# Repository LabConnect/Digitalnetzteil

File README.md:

Digitalnetzteil
============

In diesem Repository werden die Daten zum Digitalnetzteil zu finden sein.

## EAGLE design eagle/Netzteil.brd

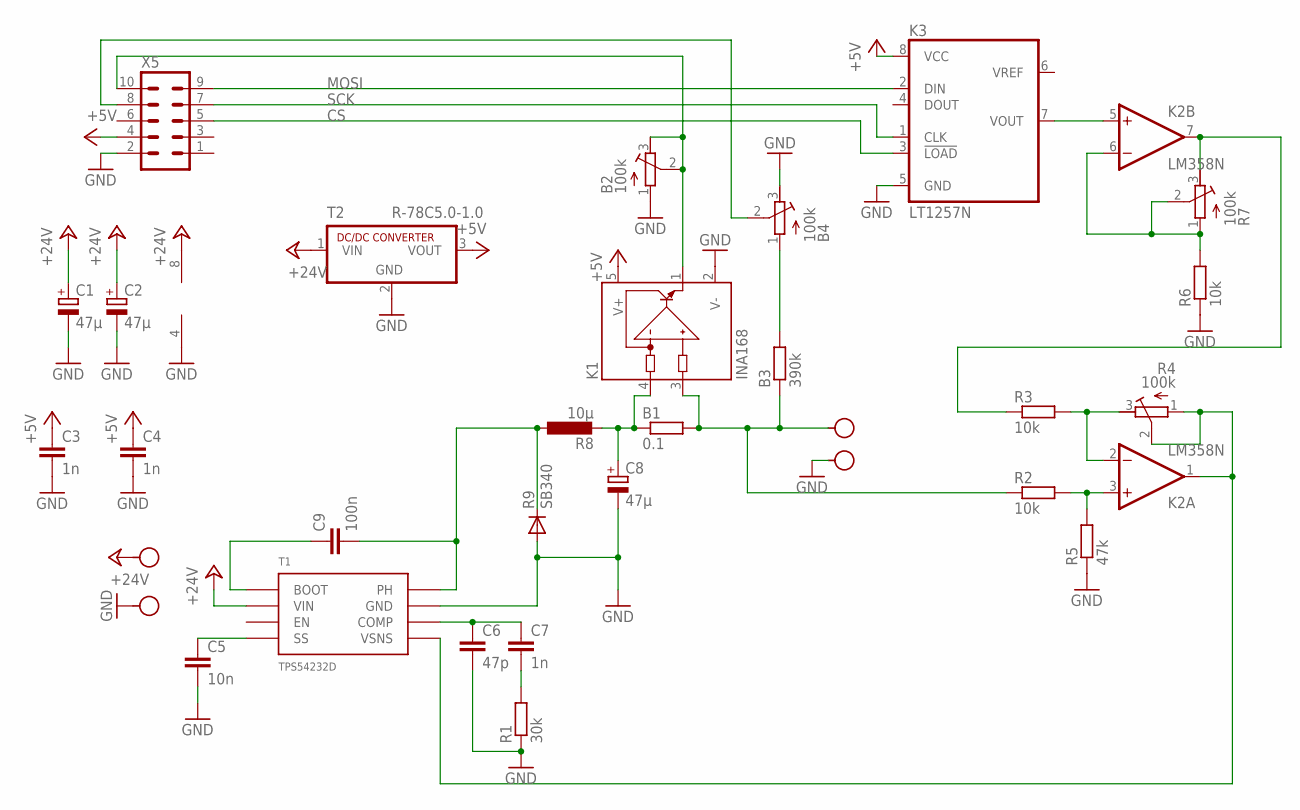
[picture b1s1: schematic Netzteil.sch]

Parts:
B1: 0.1; P0817/22
B2, B4: 100k; RTRIM64Y
B3: 390k; 0309/12
C1, C2, C8: 47µ; E2,5-6
C3, C4, C7: 1n; C025-025X050
C5: 10n; C025-025X050
C6: 47p; C025-025X050
C9: 100n; C025-025X050
K1: INA168; SOT23-5
K2: LM358N; DIL08
K3: LT1257N; DIL08
R1: 30k; 0309/12
R2, R3, R6: 10k; 0309/12
R4, R7: 100k; RTRIM64Y
R5: 47k; 0309/12
R8: 10µ; PIS2816
R9: SB340; DO201-15
T1: TPS54232D; SOIC-8
T2: R-78C5.0-1.0; SIP3; MPN R-78C5.0-1.0
X1, X2, X3, X4: SEW_HOLE-SMALL; SIMPLE_HOLE_SM
X5: ML10

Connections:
+5V: C3.1, C4.1, K1.5 (V+), K3.8 (VCC), T2.3 (VOUT), X5.4
+24V: C1.+, C2.+, K2.8 (V+), T1.2 (VIN), T2.1 (VIN), X1.P$1
CS: K3.3 (!LOAD), X5.5
GND: B2.1 (E), B4.3 (A), C1.-, C2.-, C3.2, C4.2, C5.2, C6.2, C8.-, K1.2 (V-), K2.4 (V-), K3.5 (GND), R1.1, R5.1, R6.1, R9.A, T1.7 (GND), T2.2 (GND), X2.P$1, X4.P$1, X5.2
MOSI: K3.2 (DIN), X5.9
unnamed: B1.1, C8.+, K1.4 (IN-), R8.2
unnamed: C9.2, R8.1, R9.C, T1.8 (PH)
unnamed: C5.1, T1.4 (SS)
unnamed: K2.7 (OUT), R3.1, R7.3 (A)
unnamed: C7.2, R1.2
unnamed: B1.2, B3.1, K1.3 (IN+), R2.1, X3.P$1
unnamed: C6.1, C7.1, T1.6 (COMP)
unnamed: B3.2, B4.1 (E)
unnamed: B4.2 (S), X5.8
unnamed: K2.1 (OUT), R4.1 (E), R4.2 (S), T1.5 (VSNS)
unnamed: K2.5 (+IN), K3.7 (VOUT)
unnamed: K2.6 (-IN), R6.2, R7.1 (E), R7.2 (S)
unnamed: K2.2 (-IN), R3.2, R4.3 (A)
unnamed: K2.3 (+IN), R2.2, R5.2
unnamed: B2.2 (S), B2.3 (A), K1.1 (OUT), X5.10
unnamed: C9.1, T1.1 (BOOT)
SCK: K3.1 (CLK), X5.7

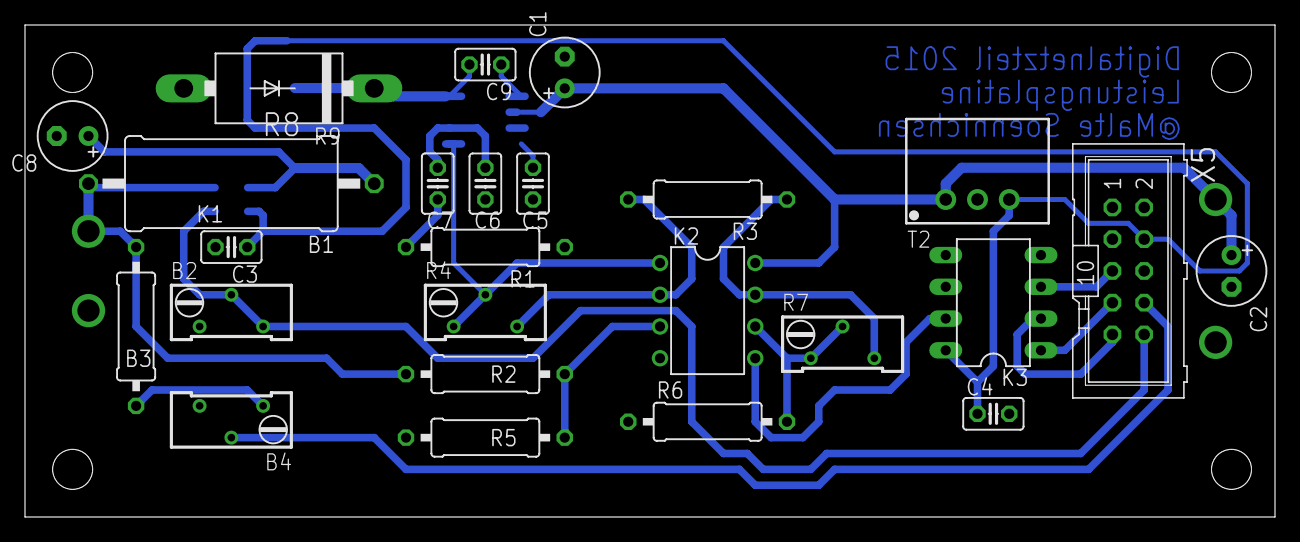
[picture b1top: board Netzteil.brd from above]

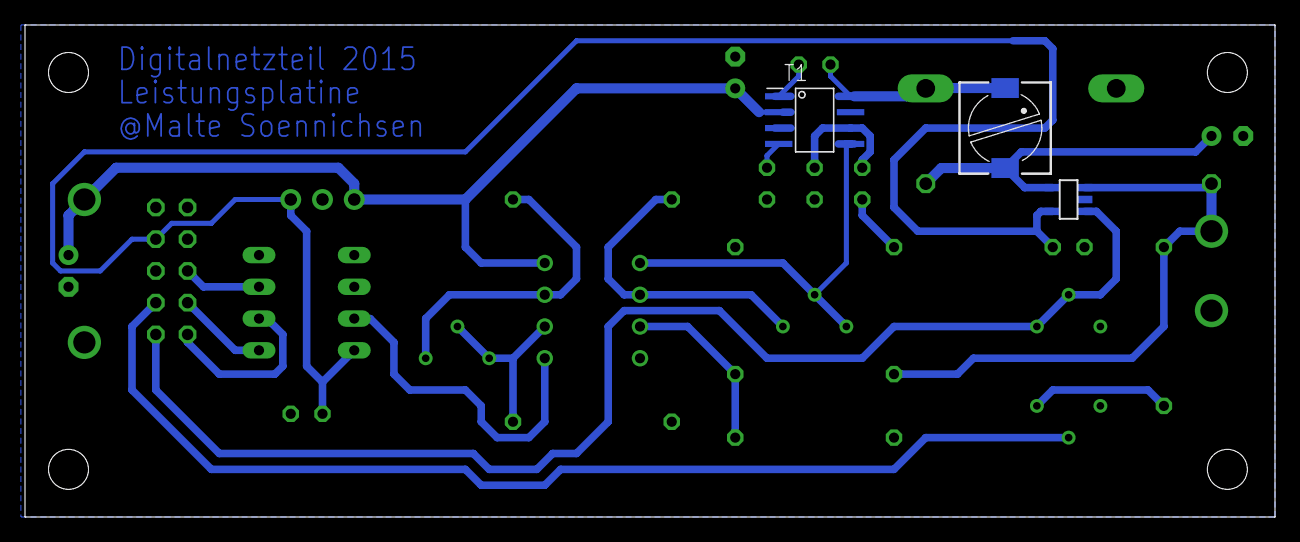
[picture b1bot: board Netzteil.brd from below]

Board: 1 copper layer, 100.0 x 39.4 mm, 32 parts (3 on the bottom side), 22 nets.

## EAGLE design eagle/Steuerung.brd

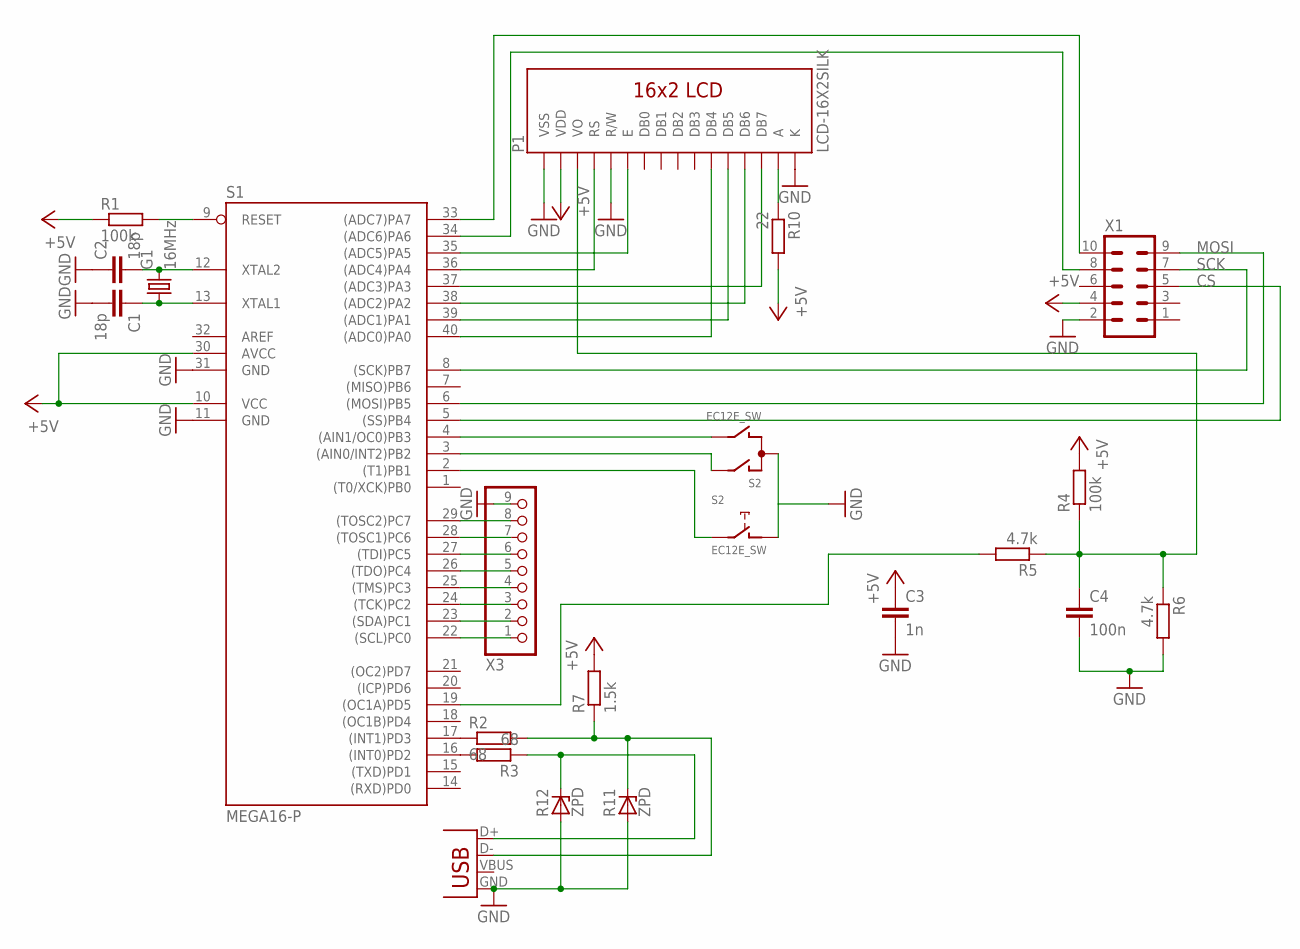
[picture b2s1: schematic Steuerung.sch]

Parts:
C1, C2: 18p; C2.5-3
C3: 1n; C1206K
C4: 100n; C1206K
G1: 16MHz; HC18U-V
P1: LCD-16X2SILK; LCD-16X2
R1, R4: 100k; R1206W
R2, R3: 68; 0309/12
R5, R6: 4.7k; R1206W
R7: 1.5k; 0309/12
R10: 22; 0309/12
R11, R12: ZPD; DO35Z10
S1: MEGA16-P; DIL40
S2: EC12E_SW; ALPS_EC12E_SW
X1: ML10
X2: USBPTH-VERTICAL; USB-B-PTH-VERTICAL
X3: PINHD-1X9; 1X09

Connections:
+5V: C3.1, P1.2 (VDD), R1.1, R4.2, R7.2, R10.2, S1.10 (VCC), S1.30 (AVCC), X1.4
CS: S1.5 ((SS)PB4), X1.5
GND: C1.2, C2.1, C3.2, C4.2, P1.1 (VSS), P1.5 (R/W), P1.16 (K), R6.2, R11.A, R12.A, S1.11 (GND), S1.31 (GND), S2.C, S2.D (1), X1.2, X2.GND, X3.9
KONTRAST: C4.1, P1.3 (VO), R4.1, R5.1, R6.1
MOSI: S1.6 ((MOSI)PB5), X1.9
unnamed: S1.34 ((ADC6)PA6), X1.8
unnamed: S1.4 ((AIN1/OC0)PB3), S2.B
unnamed: S1.3 ((AIN0/INT2)PB2), S2.A
unnamed: S1.2 ((T1)PB1), S2.E (2)
unnamed: R1.2, S1.9 (RESET)
unnamed: P1.14 (DB7), S1.37 ((ADC3)PA3)
unnamed: P1.4 (RS), S1.36 ((ADC4)PA4)
unnamed: P1.6 (E), S1.35 ((ADC5)PA5)
unnamed: P1.13 (DB6), S1.38 ((ADC2)PA2)
unnamed: P1.12 (DB5), S1.39 ((ADC1)PA1)
unnamed: P1.11 (DB4), S1.40 ((ADC0)PA0)
unnamed: P1.15 (A), R10.1
unnamed: S1.33 ((ADC7)PA7), X1.10
unnamed: S1.29 ((TOSC2)PC7), X3.8
unnamed: S1.28 ((TOSC1)PC6), X3.7
unnamed: S1.27 ((TDI)PC5), X3.6
unnamed: S1.26 ((TDO)PC4), X3.5
unnamed: S1.25 ((TMS)PC3), X3.4
unnamed: S1.24 ((TCK)PC2), X3.3
unnamed: S1.23 ((SDA)PC1), X3.2
unnamed: S1.22 ((SCL)PC0), X3.1
unnamed: C1.1, G1.1, S1.13 (XTAL1)
unnamed: C2.2, G1.2, S1.12 (XTAL2)
unnamed: R3.2, S1.16 ((INT0)PD2)
unnamed: R2.1, S1.17 ((INT1)PD3)
unnamed: R3.1, R12.C, X2.D+
unnamed: R2.2, R7.1, R11.C, X2.D-
PWM: R5.2, S1.19 ((OC1A)PD5)
SCK: S1.8 ((SCK)PB7), X1.7

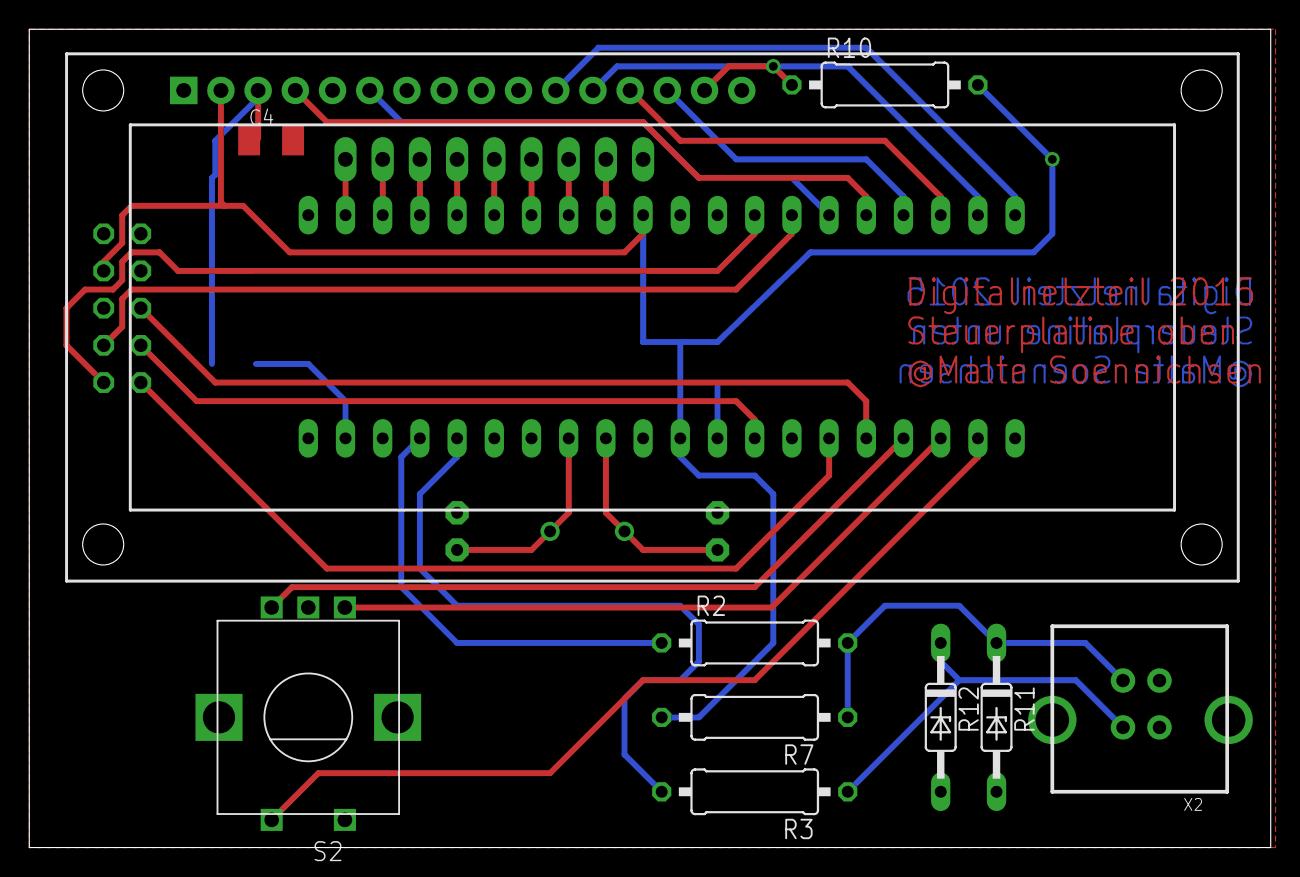
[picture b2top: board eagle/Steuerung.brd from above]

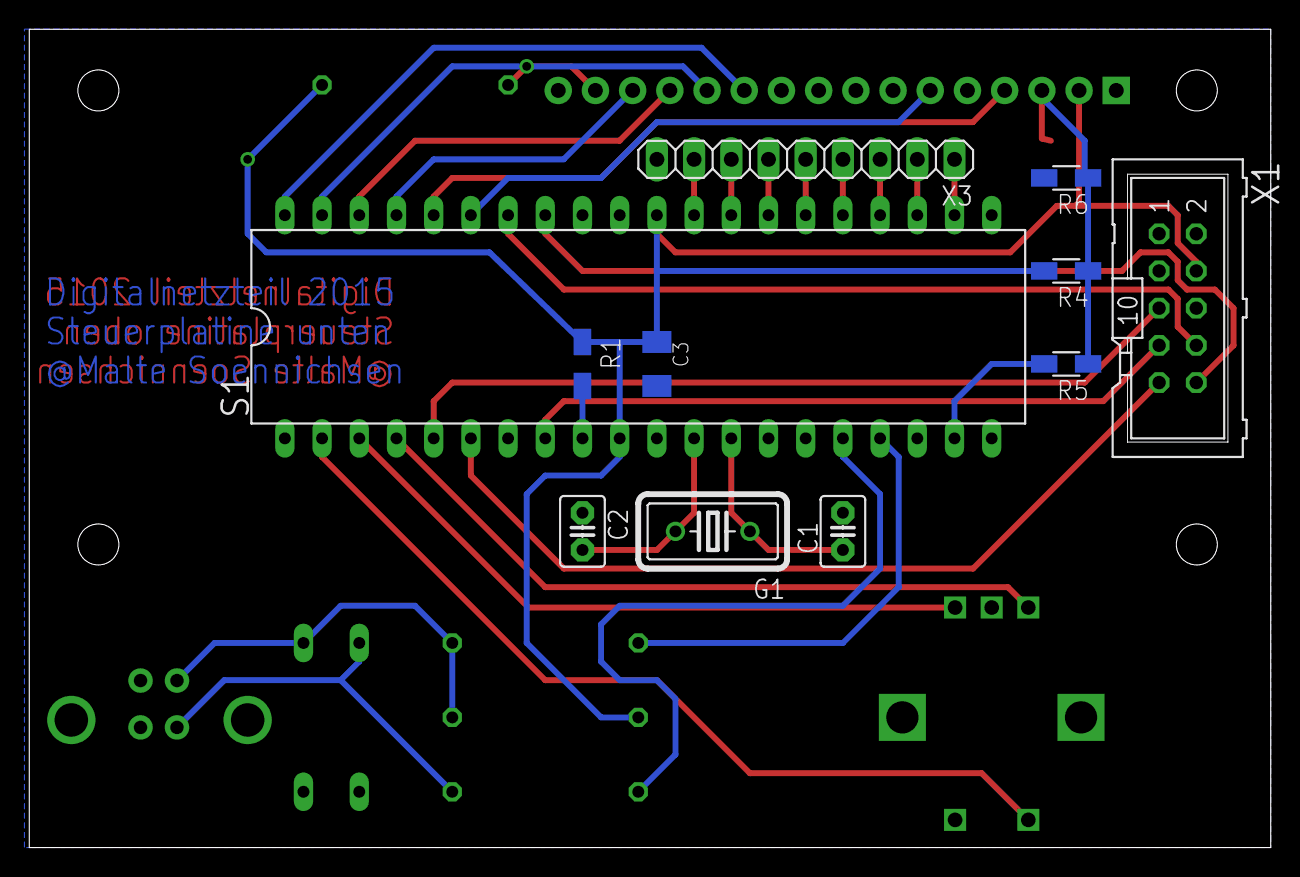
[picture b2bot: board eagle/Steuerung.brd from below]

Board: 2 copper layers, 84.8 x 55.9 mm, 21 parts (11 on the bottom side), 34 nets.

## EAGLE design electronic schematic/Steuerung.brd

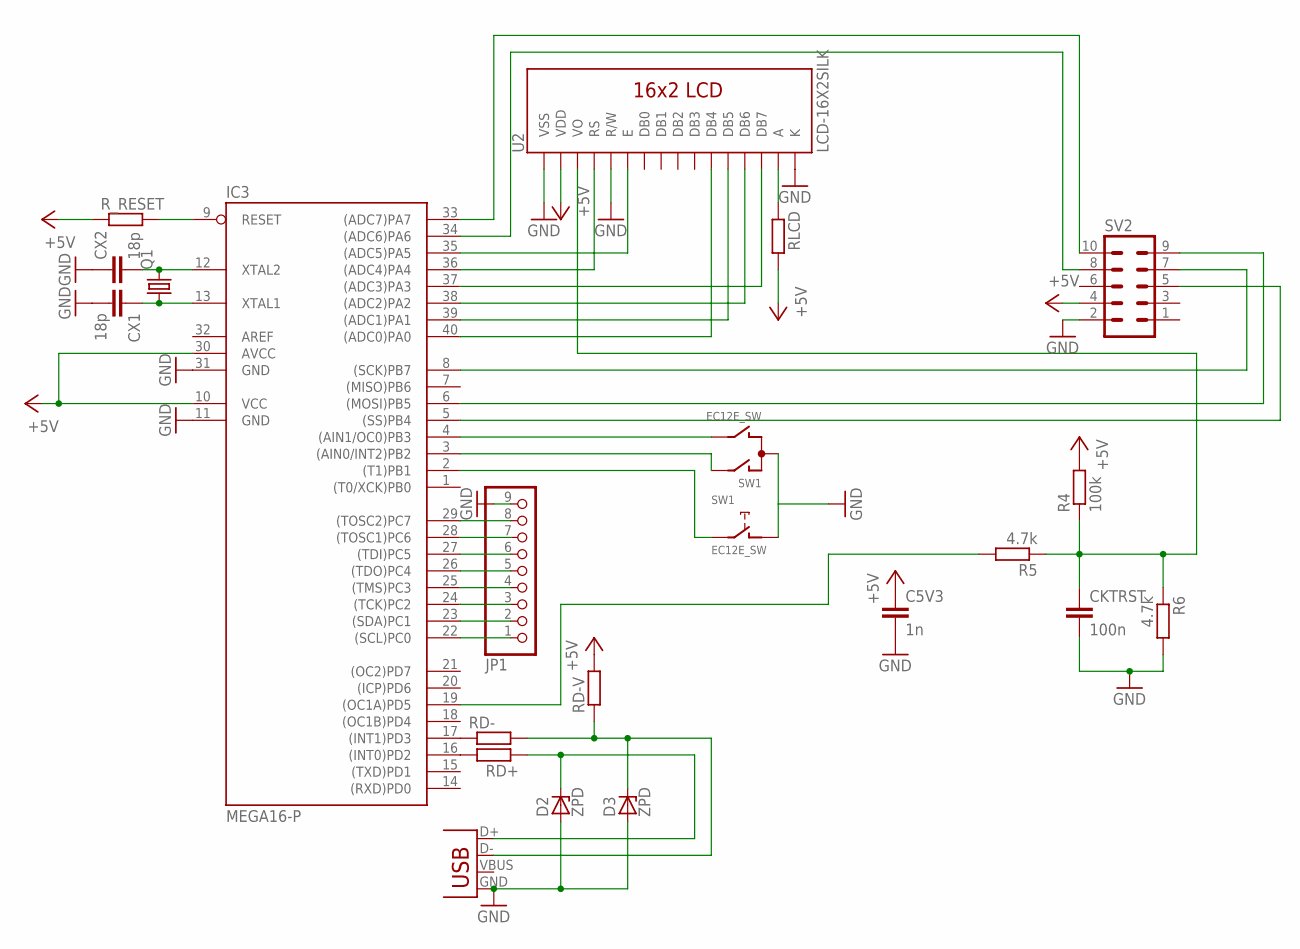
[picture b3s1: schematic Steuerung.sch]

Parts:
C5V3: 1n; C1206K
CKTRST: 100n; C1206K
CX1, CX2: 18p; C2.5-3
D2, D3: ZPD; DO35Z10
IC3: MEGA16-P; DIL40
JP1: PINHD-1X9; 1X09
JP2: USBPTH-VERTICAL; USB-B-PTH-VERTICAL
Q1: CRYSTALHC18U-V; HC18U-V
R4: 100k; R1206W
R5, R6: 4.7k; R1206W
RD+: R-EU_0309/12; 0309/12
RD-: R-EU_0309/12; 0309/12
RD-V: R-EU_0309/12; 0309/12
RLCD: R-EU_0309/12; 0309/12
R_RESET: R-EU_R1206W; R1206W
SV2: ML10
SW1: EC12E_SW; ALPS_EC12E_SW
U2: LCD-16X2SILK; LCD-16X2

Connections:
+5V: C5V3.1, IC3.10 (VCC), IC3.30 (AVCC), R4.2, RD-V.2, RLCD.2, R_RESET.1, SV2.4, U2.2 (VDD)
GND: C5V3.2, CKTRST.2, CX1.2, CX2.1, D2.A, D3.A, IC3.11 (GND), IC3.31 (GND), JP1.9, JP2.GND, R6.2, SV2.2, SW1.C, SW1.D (1), U2.1 (VSS), U2.5 (R/W), U2.16 (K)
KONTRAST: CKTRST.1, R4.1, R5.1, R6.1, U2.3 (VO)
unnamed: IC3.34 ((ADC6)PA6), SV2.8
unnamed: IC3.4 ((AIN1/OC0)PB3), SW1.B
unnamed: IC3.3 ((AIN0/INT2)PB2), SW1.A
unnamed: IC3.2 ((T1)PB1), SW1.E (2)
unnamed: IC3.9 (RESET), R_RESET.2
unnamed: IC3.37 ((ADC3)PA3), U2.14 (DB7)
unnamed: IC3.36 ((ADC4)PA4), U2.4 (RS)
unnamed: IC3.35 ((ADC5)PA5), U2.6 (E)
unnamed: IC3.38 ((ADC2)PA2), U2.13 (DB6)
unnamed: IC3.39 ((ADC1)PA1), U2.12 (DB5)
unnamed: IC3.40 ((ADC0)PA0), U2.11 (DB4)
unnamed: RLCD.1, U2.15 (A)
unnamed: IC3.33 ((ADC7)PA7), SV2.10
unnamed: IC3.5 ((SS)PB4), SV2.5
unnamed: IC3.8 ((SCK)PB7), SV2.7
unnamed: IC3.6 ((MOSI)PB5), SV2.9
unnamed: IC3.29 ((TOSC2)PC7), JP1.8
unnamed: IC3.28 ((TOSC1)PC6), JP1.7
unnamed: IC3.27 ((TDI)PC5), JP1.6
unnamed: IC3.26 ((TDO)PC4), JP1.5
unnamed: IC3.25 ((TMS)PC3), JP1.4
unnamed: IC3.24 ((TCK)PC2), JP1.3
unnamed: IC3.23 ((SDA)PC1), JP1.2
unnamed: IC3.22 ((SCL)PC0), JP1.1
unnamed: CX1.1, IC3.13 (XTAL1), Q1.1
unnamed: CX2.2, IC3.12 (XTAL2), Q1.2
unnamed: IC3.16 ((INT0)PD2), RD+.2
unnamed: IC3.17 ((INT1)PD3), RD-.1
unnamed: D2.C, JP2.D+, RD+.1
unnamed: D3.C, JP2.D-, RD-.2, RD-V.1
PWM: IC3.19 ((OC1A)PD5), R5.2

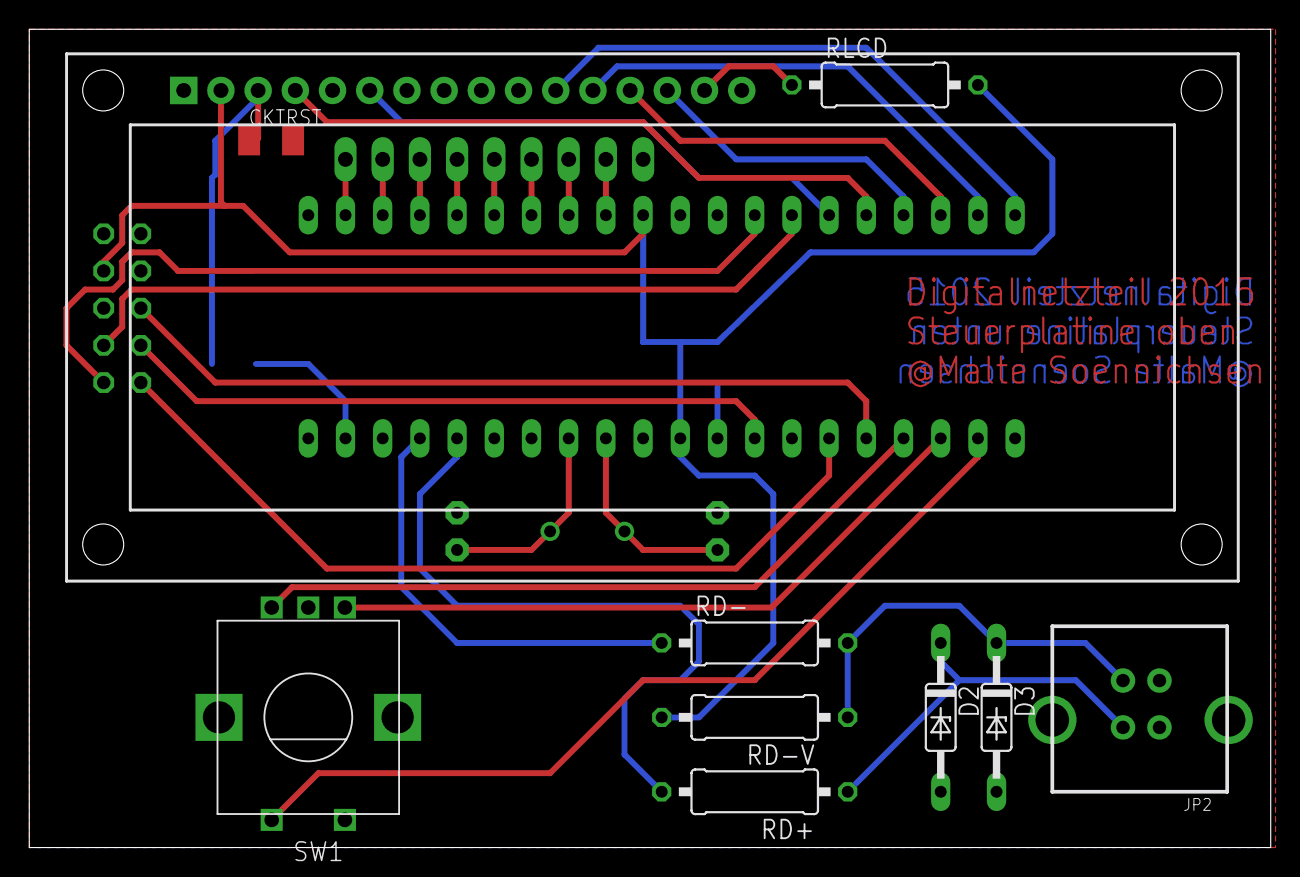
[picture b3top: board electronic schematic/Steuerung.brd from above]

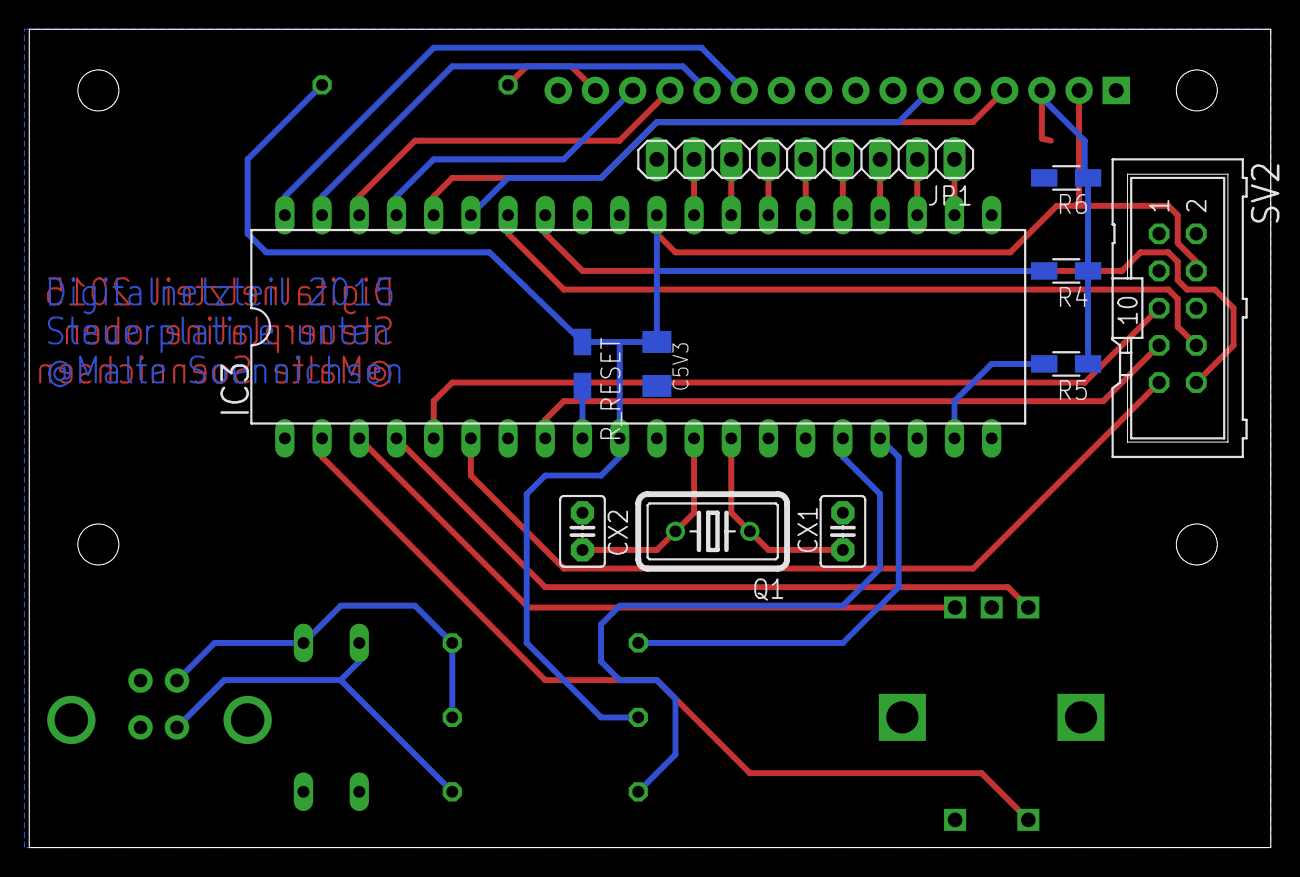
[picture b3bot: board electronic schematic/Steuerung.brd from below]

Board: 2 copper layers, 84.8 x 55.9 mm, 21 parts (11 on the bottom side), 34 nets.

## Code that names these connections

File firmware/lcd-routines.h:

// Ansteuerung eines HD44780 kompatiblen LCD im 4-Bit-Interfacemodus
// http://www.mikrocontroller.net/articles/AVR-GCC-Tutorial/LCD-Ansteuerung
//
 
#ifndef LCD_ROUTINES_H
#define LCD_ROUTINES_H
 
////////////////////////////////////////////////////////////////////////////////
// Hier die verwendete Taktfrequenz in Hz eintragen, wichtig!
 
#ifndef F_CPU
#define F_CPU 16000000
#endif
 
////////////////////////////////////////////////////////////////////////////////
// Pinbelegung für das LCD, an verwendete Pins anpassen
// Alle LCD Pins müssen an einem Port angeschlossen sein und die 4
// Datenleitungen müssen auf aufeinanderfolgenden Pins liegen
 
//  LCD DB4-DB7 <-->  PORTD Bit PD0-PD3
#define LCD_PORT      PORTA
#define LCD_DDR       DDRA
#define LCD_DB        PA0
 
//  LCD RS      <-->  PORTD Bit PD4     (RS: 1=Data, 0=Command)
#define LCD_RS        PA4
 
//  LCD EN      <-->  PORTD Bit PD5     (EN: 1-Impuls für Daten)
#define LCD_EN        PA5
 
////////////////////////////////////////////////////////////////////////////////
// LCD Ausführungszeiten (MS=Millisekunden, US=Mikrosekunden)
 
#define LCD_BOOTUP_MS           15
#define LCD_ENABLE_US           20
#define LCD_WRITEDATA_US        46
#define LCD_COMMAND_US          42
 
#define LCD_SOFT_RESET_MS1      5
#define LCD_SOFT_RESET_MS2      1
#define LCD_SOFT_RESET_MS3      1
#define LCD_SET_4BITMODE_MS     5
 
#define LCD_CLEAR_DISPLAY_MS    2
#define LCD_CURSOR_HOME_MS      2
 
////////////////////////////////////////////////////////////////////////////////
// Zeilendefinitionen des verwendeten LCD
// Die Einträge hier sollten für ein LCD mit einer Zeilenlänge von 16 Zeichen passen
// Bei anderen Zeilenlängen müssen diese Einträge angepasst werden
 
#define LCD_DDADR_LINE1         0x00
#define LCD_DDADR_LINE2         0x40
#define LCD_DDADR_LINE3         0x10
#define LCD_DDADR_LINE4         0x50
 
////////////////////////////////////////////////////////////////////////////////
// Initialisierung: muss ganz am Anfang des Programms aufgerufen werden.
void lcd_init( void );
 
////////////////////////////////////////////////////////////////////////////////
// LCD löschen
void lcd_clear( void );
 
////////////////////////////////////////////////////////////////////////////////
// Cursor in die 1. Zeile, 0-te Spalte
void lcd_home( void );
 
////////////////////////////////////////////////////////////////////////////////
// Cursor an eine beliebige Position 
void lcd_setcursor( uint8_t spalte, uint8_t zeile );
 
////////////////////////////////////////////////////////////////////////////////
// Ausgabe eines einzelnen Zeichens an der aktuellen Cursorposition 
void lcd_data( uint8_t data );
 
////////////////////////////////////////////////////////////////////////////////
// Ausgabe eines Strings an der aktuellen Cursorposition 
void lcd_string( const char *data );
 
////////////////////////////////////////////////////////////////////////////////
// Definition eines benutzerdefinierten Sonderzeichens.
// data muss auf ein Array[8] mit den Zeilencodes des zu definierenden Zeichens
// zeigen
void lcd_generatechar( uint8_t code, const uint8_t *data );
 
////////////////////////////////////////////////////////////////////////////////
// Ausgabe eines Kommandos an das LCD.
void lcd_command( uint8_t data );
 
 
////////////////////////////////////////////////////////////////////////////////
// LCD Befehle und Argumente.
// Zur Verwendung in lcd_command
 
// Clear Display -------------- 0b00000001
#define LCD_CLEAR_DISPLAY       0x01
 
// Cursor Home ---------------- 0b0000001x
#define LCD_CURSOR_HOME         0x02
 
// Set Entry Mode ------------- 0b000001xx
#define LCD_SET_ENTRY           0x04
 
#define LCD_ENTRY_DECREASE      0x00
#define LCD_ENTRY_INCREASE      0x02
#define LCD_ENTRY_NOSHIFT       0x00
#define LCD_ENTRY_SHIFT         0x01
 
// Set Display ---------------- 0b00001xxx
#define LCD_SET_DISPLAY         0x08
 
#define LCD_DISPLAY_OFF         0x00
#define LCD_DISPLAY_ON          0x04
#define LCD_CURSOR_OFF          0x00
#define LCD_CURSOR_ON           0x02
#define LCD_BLINKING_OFF        0x00
#define LCD_BLINKING_ON         0x01
 
// Set Shift ------------------ 0b0001xxxx
#define LCD_SET_SHIFT           0x10
 
#define LCD_CURSOR_MOVE         0x00
#define LCD_DISPLAY_SHIFT       0x08
#define LCD_SHIFT_LEFT          0x00
#define LCD_SHIFT_RIGHT         0x04
 
// Set Function --------------- 0b001xxxxx
#define LCD_SET_FUNCTION        0x20
 
#define LCD_FUNCTION_4BIT       0x00
#define LCD_FUNCTION_8BIT       0x10
#define LCD_FUNCTION_1LINE      0x00
#define LCD_FUNCTION_2LINE      0x08
#define LCD_FUNCTION_5X7        0x00
#define LCD_FUNCTION_5X10       0x04
 
#define LCD_SOFT_RESET          0x30
 
// Set CG RAM Address --------- 0b01xxxxxx  (Character Generator RAM)
#define LCD_SET_CGADR           0x40
 
#define LCD_GC_CHAR0            0
#define LCD_GC_CHAR1            1
#define LCD_GC_CHAR2            2
#define LCD_GC_CHAR3            3
#define LCD_GC_CHAR4            4
#define LCD_GC_CHAR5            5
#define LCD_GC_CHAR6            6
#define LCD_GC_CHAR7            7
 
// Set DD RAM Address --------- 0b1xxxxxxx  (Display Data RAM)
#define LCD_SET_DDADR           0x80
 
#endif

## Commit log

2014-12-14 Schematic
2015-02-05 HID USB Protokoll Test in Qt
2015-03-18 powersupply control
2015-03-18 new layout and schematic
2015-03-18 function test for usb, spi, rotary encoder and lcd
2015-04-07 change the vid and pid
2015-06-08 Final
2015-06-08 Remove old directorys

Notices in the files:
parts and their libraries:
LilyPad-Wearables: Licensing:Creative Commons ShareAlike 4.0 International - https://creativecommons.org/licenses/by-sa/4.0
Volks73-TexasInstruments: Creative Commons Attribution-ShareAlike 3.0 Unported (CC BY-SA 3.0), http://creativecommons.org/licenses/by-sa/3.0/.
